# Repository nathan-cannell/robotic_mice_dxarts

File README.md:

# Robotic Mice DXARTS Exhibit

This repository documents the Robotic Mice project, an interactive art installation for the University of Washington's DXARTS program. The exhibit features 25 autonomous robot mice that navigate their environment, avoid human presence, and seek out darkness.

---

## Overview

The Robotic Mice project explores the intersection of robotics, art, and emergent behavior. Each mouse is equipped with sensors and programmed to:

- Move autonomously within the exhibit space
- Avoid humans and other obstacles
- Seek out darker areas, simulating natural rodent behavior

The collective movement of the mice creates a dynamic, unpredictable environment that invites audience interaction and reflection on the boundaries between artificial and natural life.

---

## Team

| Name            | Group           |
|-----------------|----------------|
| Sep Makhsous    | ECE Professor  |
| Eunsun Choi     | DXARTS Student |
| Ethan Widger    | ECE Student    |
| Daniela Berreth | CSE Student    |
| Nathan Cannell  | ECE Student    |
| Sam Han         | ECE Student    |
| Martin Li       | ECE Student    |

---

## System Architecture

The project leverages ROS 2 for distributed control and communication between the 25 robot mice. Key components include:

- **Autonomous Navigation:** Each mouse runs its own navigation stack, using sensor input to avoid obstacles and seek darkness.
- **Dynamic Namespace Assignment:** Mice are dynamically assigned unique namespaces for communication using an ID service.
- **Multi-Robot Coordination:** Centralized "mux" nodes aggregate status information (e.g., fuel/battery, presence) from all mice for monitoring and exhibit control.
- **Localization:** Each mouse runs an EKF-based localization node within its namespace to estimate its pose.

---

## Main Code Structure

### 1. Launching the System

The system is launched using ROS 2 launch files that start the ID assignment service, presence and fuel monitoring muxes, and localization nodes for each mouse.

**`mouse.launch.py` (excerpt):**
from launch import LaunchDescription
from launch_ros.actions import Node

def generate_launch_description():
ld = LaunchDescription()
mouse_id_service = Node(
    package='mouse_global',
    executable='id_service',
    name='id_service',
)
ld.add_action(mouse_id_service)

presence_mux = Node(
    package='mouse_global',
    executable='presence_mux',
    name='presence',
)
ld.add_action(presence_mux)

fuel_mux = Node(
    package='mouse_global',
    executable='fuel_monitor',
    name='fuel_monitor',
)
ld.add_action(fuel_mux)

return ld
[6]

### 2. Mouse Namespace Management

Namespaces are assigned dynamically to each mouse using a custom ROS service that ensures each robot receives a unique identifier.

**`id_srv.py` (excerpt):**
class ID_Assigner(Node):
def init(self):
super().init('mouse_global')
self.srv = self.create_service(Id, 'id_assign', self.id_request_callback)
[2]

### 3. Presence and Fuel Monitoring

Centralized mux nodes subscribe to all `/mouse_X/presence` and `/mouse_X/fuel` topics, aggregating this data for exhibit monitoring and safety.

- **PresenceMUX:** Publishes a combined presence signal and logs activity of each mouse.
- **FuelMUX:** Monitors battery levels and warns if any mouse is critically low on power.

**`presence_mux.py` and `fuel_mux.py` (excerpts):**
PresenceMUX subscribes to all /mouse_X/presence topics and publishes /presence_mux
class PresenceMUX(Node):
...
def connect(self):
mouse_topics = get_mouse_topics(self, "presence") [4]
# Subscribe to each topic

FuelMUX subscribes to all /mouse_X/fuel topics and monitors battery levels
class FuelMUX(Node):
...
def connect(self):
mouse_topics = get_mouse_topics(self, "fuel") [1]

### 4. Localization

Each mouse runs an EKF-based localization node within its namespace, as defined in `localization.launch.py`.

**`localization.launch.py` (excerpt):**
from launch import LaunchDescription
from launch_ros.actions import Node

def generate_launch_description():
ld = LaunchDescription()
mouse_namespaces = ['/mouse_1', '/mouse_2']
for namespace in mouse_namespaces:
robot_localization_node = Node(
package='robot_localization',
executable='ekf_node',
name='ekf_filter_node',
namespace=namespace)

ld.add_action(robot_localization_node)

return ld
[5]

---

## How to Run

1. **Install Dependencies:** Ensure ROS 2 and all required Python packages are installed.
2. **Build the Workspace:**
colcon build
source install/setup.bash
3. **Launch the System:**
ros2 launch mouse.launch.py
This will start the ID service, monitoring muxes, and (with additional configuration) the navigation and localization nodes for each mouse.

---

## Customization

- **Number of Mice:** The system supports dynamic scaling. Update the list of namespaces or use the ID service to add/remove mice as needed.
- **Behavior Tuning:** Modify the navigation and sensor processing scripts to adjust how mice respond to light, obstacles, or presence.

---

## Acknowledgments

This project was made possible by the collaborative efforts of students and faculty from UW's DXARTS, ECE, and CSE departments.

---

## Contact

For questions or collaboration inquiries, please contact the project team via the University of Washington DXARTS program.

---

**Enjoy exploring the emergent, collective behavior of our robotic mice!**

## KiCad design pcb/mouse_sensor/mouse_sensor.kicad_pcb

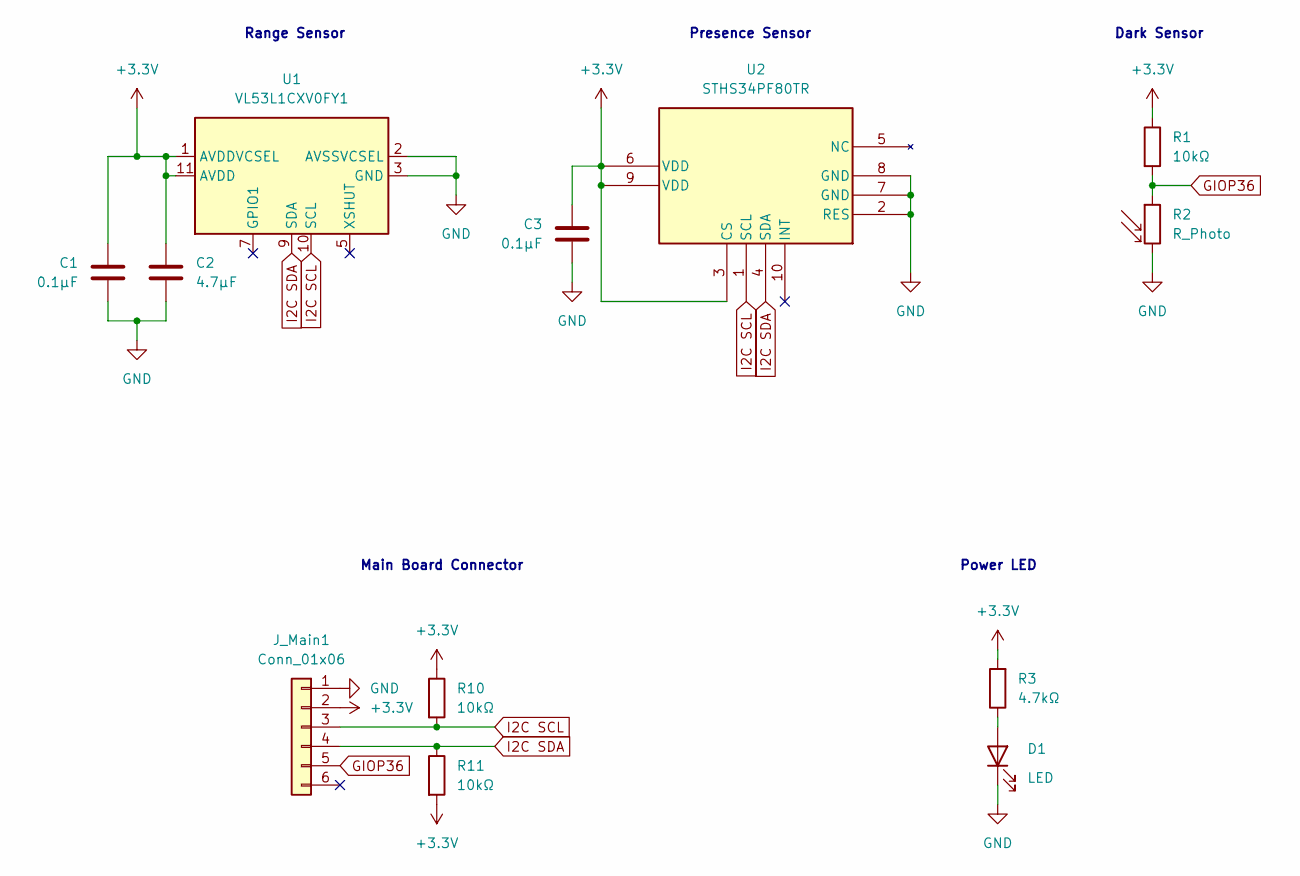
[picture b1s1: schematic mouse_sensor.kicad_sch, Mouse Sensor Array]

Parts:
C1, C3: 0.1µF; C_0402_1005Metric
C2: 4.7µF; C_0805_2012Metric
D1: LED; LED_0603_1608Metric
J_Main1: Conn_01x06; PinHeader_1x06_P2.54mm_Vertical
R1, R10, R11: 10kΩ; R_0603_1608Metric
R2: R_Photo; R_LDR_5.1x4.3mm_P3.4mm_Vertical
R3: 4.7kΩ; R_0603_1608Metric
U1: VL53L1CXV0FY1; ST_VL53L1x
U2: STHS34PF80TR; OLGA-10_3P2X4P2_STM

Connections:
+3.3V: C1.1, C2.1, C3.1, J_Main1.2, R1.1, R3.2, R10.1, R11.2, U1.1 (AVDDVCSEL), U1.11 (AVDD), U2.3 (CS), U2.6 (VDD), U2.9 (VDD)
GIOP36: J_Main1.5, R1.2, R2.1
GND: C1.2, C2.2, C3.2, D1.1 (K), J_Main1.1, R2.2, U1.2 (AVSSVCSEL), U1.3 (GND), U1.4 (GND), U1.6 (GND), U1.12 (GND), U2.2 (RES), U2.7 (GND), U2.8 (GND)
I2C SCL: J_Main1.3, R10.2, U1.10 (SCL), U2.1 (SCL)
I2C SDA: J_Main1.4, R11.1, U1.9 (SDA), U2.4 (SDA)
unnamed: D1.2 (A), R3.1

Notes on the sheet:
Dark Sensor
Power LED
Main Board Connector
Presence Sensor
Range Sensor

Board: 2 copper layers, 12 parts (0 on the bottom side), 6 nets, no tracks yet.

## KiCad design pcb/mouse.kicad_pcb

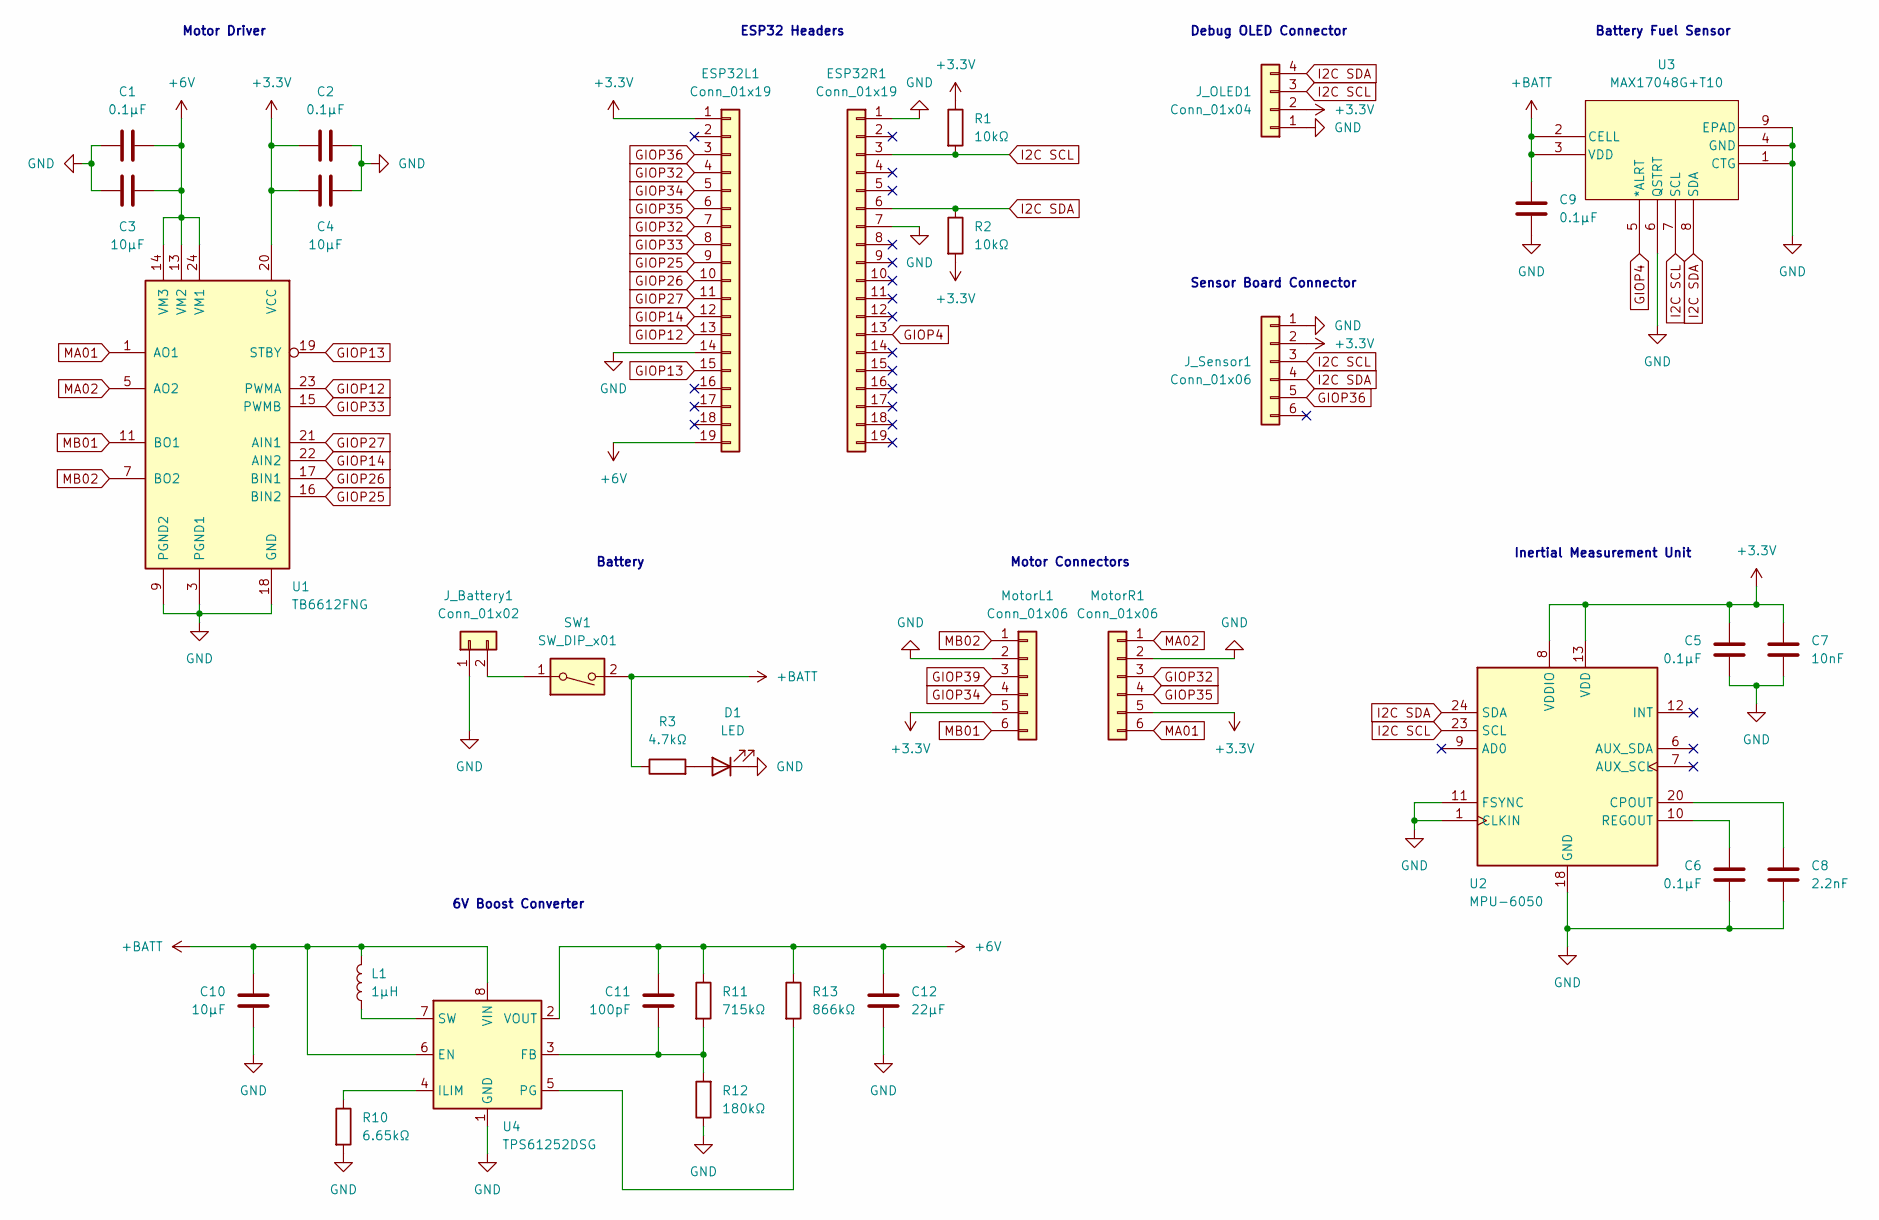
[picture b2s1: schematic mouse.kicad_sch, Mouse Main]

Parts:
C1, C2, C5, C6, C9: 0.1µF; C_0402_1005Metric
C3, C4, C10: 10µF; C_0603_1608Metric
C7: 10nF; C_0201_0603Metric
C8: 2.2nF; C_0603_1608Metric
C11: 100pF; C_0603_1608Metric
C12: 22µF; C_1210_3225Metric
D1: LED; LED_0603_1608Metric
ESP32L1, ESP32R1: Conn_01x19; PinSocket_1x19_P2.54mm_Vertical
J_Battery1: Conn_01x02; JST_PH_B2B-PH-K_1x02_P2.00mm_Vertical
J_OLED1: Conn_01x04; PinSocket_1x04_P2.54mm_Vertical
J_Sensor1: Conn_01x06; PinSocket_1x06_P2.54mm_Horizontal
L1: 1µH; L_0805_2012Metric
MotorL1: Conn_01x06; JST_SH_BM06B-SRSS-TB_1x06-1MP_P1.00mm_Vertical
MotorR1: Conn_01x06; JST_SH_BM06B-SRSS-TB_1x06-1MP_P1.00mm_Vertical
R1, R2: 10kΩ; R_0603_1608Metric
R3: 4.7kΩ; R_0603_1608Metric
R10: 6.65kΩ; R_0603_1608Metric
R11: 715kΩ; R_0603_1608Metric
R12: 180kΩ; R_0603_1608Metric
R13: 866kΩ; R_0603_1608Metric
SW1: SW_DIP_x01; SW_CuK_OS102011MA1QN1_SPDT_Angled
U1: TB6612FNG; SSOP-24_5.3x8.2mm_P0.65mm
U2: MPU-6050; InvenSense_QFN-24_4x4mm_P0.5mm
U3: MAX17048G+T10; 21-0168E_T822-3_MXM
U4: TPS61252DSG; WSON-8-1EP_2x2mm_P0.5mm_EP0.9x1.6mm

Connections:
+3.3V: C2.1, C4.1, C5.2, C7.1, ESP32L1.1, J_OLED1.2, J_Sensor1.2, MotorL1.5, MotorR1.5, R1.1, R2.2, U1.20 (VCC), U2.8 (VDDIO), U2.13 (VDD)
+6V: C1.1, C3.2, C11.1, C12.1, ESP32L1.19, R11.1, R13.1, U1.13 (VM2), U1.14 (VM3), U1.24 (VM1), U4.2 (VOUT)
+BATT: C9.1, C10.2, L1.2, R3.1, SW1.2, U3.2 (CELL), U3.3 (VDD), U4.6 (EN), U4.8 (VIN)
GIOP4: ESP32R1.13, U3.5 (*ALRT)
GIOP12: ESP32L1.13, U1.23 (PWMA)
GIOP13: ESP32L1.15, U1.19 (STBY)
GIOP14: ESP32L1.12, U1.22 (AIN2)
GIOP25: ESP32L1.9, U1.16 (BIN2)
GIOP26: ESP32L1.10, U1.17 (BIN1)
GIOP27: ESP32L1.11, U1.21 (AIN1)
GIOP32: ESP32L1.4, ESP32L1.7, MotorR1.3
GIOP33: ESP32L1.8, U1.15 (PWMB)
GIOP34: ESP32L1.5, MotorL1.4
GIOP35: ESP32L1.6, MotorR1.4
GIOP36: ESP32L1.3, J_Sensor1.5
GIOP39: MotorL1.3
GND: C1.2, C2.2, C3.1, C4.2, C5.1, C6.1, C7.2, C8.2, C9.2, C10.1, C12.2, D1.1 (K), ESP32L1.14, ESP32R1.1, ESP32R1.7, J_Battery1.1, J_OLED1.1, J_Sensor1.1, MotorL1.2, MotorR1.2, R10.2, R12.1, U1.3 (PGND1), U1.4 (PGND1), U1.9 (PGND2), U1.10 (PGND2), U1.18 (GND), U2.1 (CLKIN), U2.11 (FSYNC), U2.18 (GND), U3.1 (CTG), U3.4 (GND), U3.6 (QSTRT), U3.9 (EPAD), U4.1 (GND), U4.9 (GND)
I2C SCL: ESP32R1.3, J_OLED1.3, J_Sensor1.3, R1.2, U2.23 (SCL), U3.7 (SCL)
I2C SDA: ESP32R1.6, J_OLED1.4, J_Sensor1.4, R2.1, U2.24 (SDA), U3.8 (SDA)
MA01: MotorR1.6, U1.1 (AO1), U1.2 (AO1)
MA02: MotorR1.1, U1.5 (AO2), U1.6 (AO2)
MB01: MotorL1.6, U1.11 (BO1), U1.12 (BO1)
MB02: MotorL1.1, U1.7 (BO2), U1.8 (BO2)
unnamed: C6.2, U2.10 (REGOUT)
unnamed: C8.1, U2.20 (CPOUT)
unnamed: C11.2, R11.2, R12.2, U4.3 (FB)
unnamed: D1.2 (A), R3.2
unnamed: J_Battery1.2, SW1.1
unnamed: L1.1, U4.7 (SW)
unnamed: R10.1, U4.4 (ILIM)
unnamed: R13.2, U4.5 (PG)

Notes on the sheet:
Motor Connectors
ESP32 Headers
Battery Fuel Sensor
Debug OLED Connector
Motor Driver
6V Boost Converter
Battery
Sensor Board Connector
Inertial Measurement Unit

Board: 2 copper layers, 33 parts (0 on the bottom side), 30 nets, no tracks yet.

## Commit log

2025-05-19 autonomous robot mice
2025-05-19 added photos and videos
2025-05-19 added global controls
